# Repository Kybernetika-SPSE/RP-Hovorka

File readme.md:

# KYB Fotaoparát - Systém pro obsluhu kamery

## Zadání projektu
Cílem práce je návrh a realizace systému pro obsluhu
digitální kamery pomocí mikrokontroléru.

## Řešitelský tým
Vít Hovorka

## Vedoucí
Jiří Švihla

## Oponent
Pavel Jedlička

## Shrnutí projektu
Projekt „Fotaoparát" má za cíl navrhnout a realizovat řídicí systém pro digitální fotoaparát založený na mikrokontroléru ESP32‑P4. Práce kombinuje návrh hardware (schemata, PCB, periferie), mechanický návrh těla a vývoj firmware pro řízení kamery, paměti a uživatelského rozhraní.
## Fáze a plnění
## Termíny
| milník                                | termín              |
| :------------------------------------ | :------------------ |
| Nastudování dokumentací, návrh zapojení a design obalu| **30.12.2025** |
| Sestavení                         | **30.1.2026**  |
| Naprogramování operačního softwaru   | **27.2. 2026** |
| Testování a tvora dokumentace        | **30.03.2026** |
| Odevzdání ročníkové práce            | **30.04.2026** |

[^1]: Změněno na základě požadavků

### Ganttův diagram postupu
```mermaid
gantt
    title Milníky projektu
    dateFormat  YYYY-MM-DD
    axisFormat  %d.%m.%Y
    section Studium a návrh
    Studovat dokumentace a návrh   :done, study, 2025-09-01, 2025-12-30
    section Sestavení prototypu
    Montáž prototypu               :build, 2026-01-01, 2026-01-30
    section Vývoj softwaru
    Implementace firmware          :dev, 2026-02-01, 2026-02-27
    section Testování a dokumentace
    Testování a tvorba dokumentace :test, 2026-03-01, 2026-03-30
    section Odevzdání a prezentace
    Finalizace a odevzdání         :deliver, 2026-04-01, 2026-04-30
```

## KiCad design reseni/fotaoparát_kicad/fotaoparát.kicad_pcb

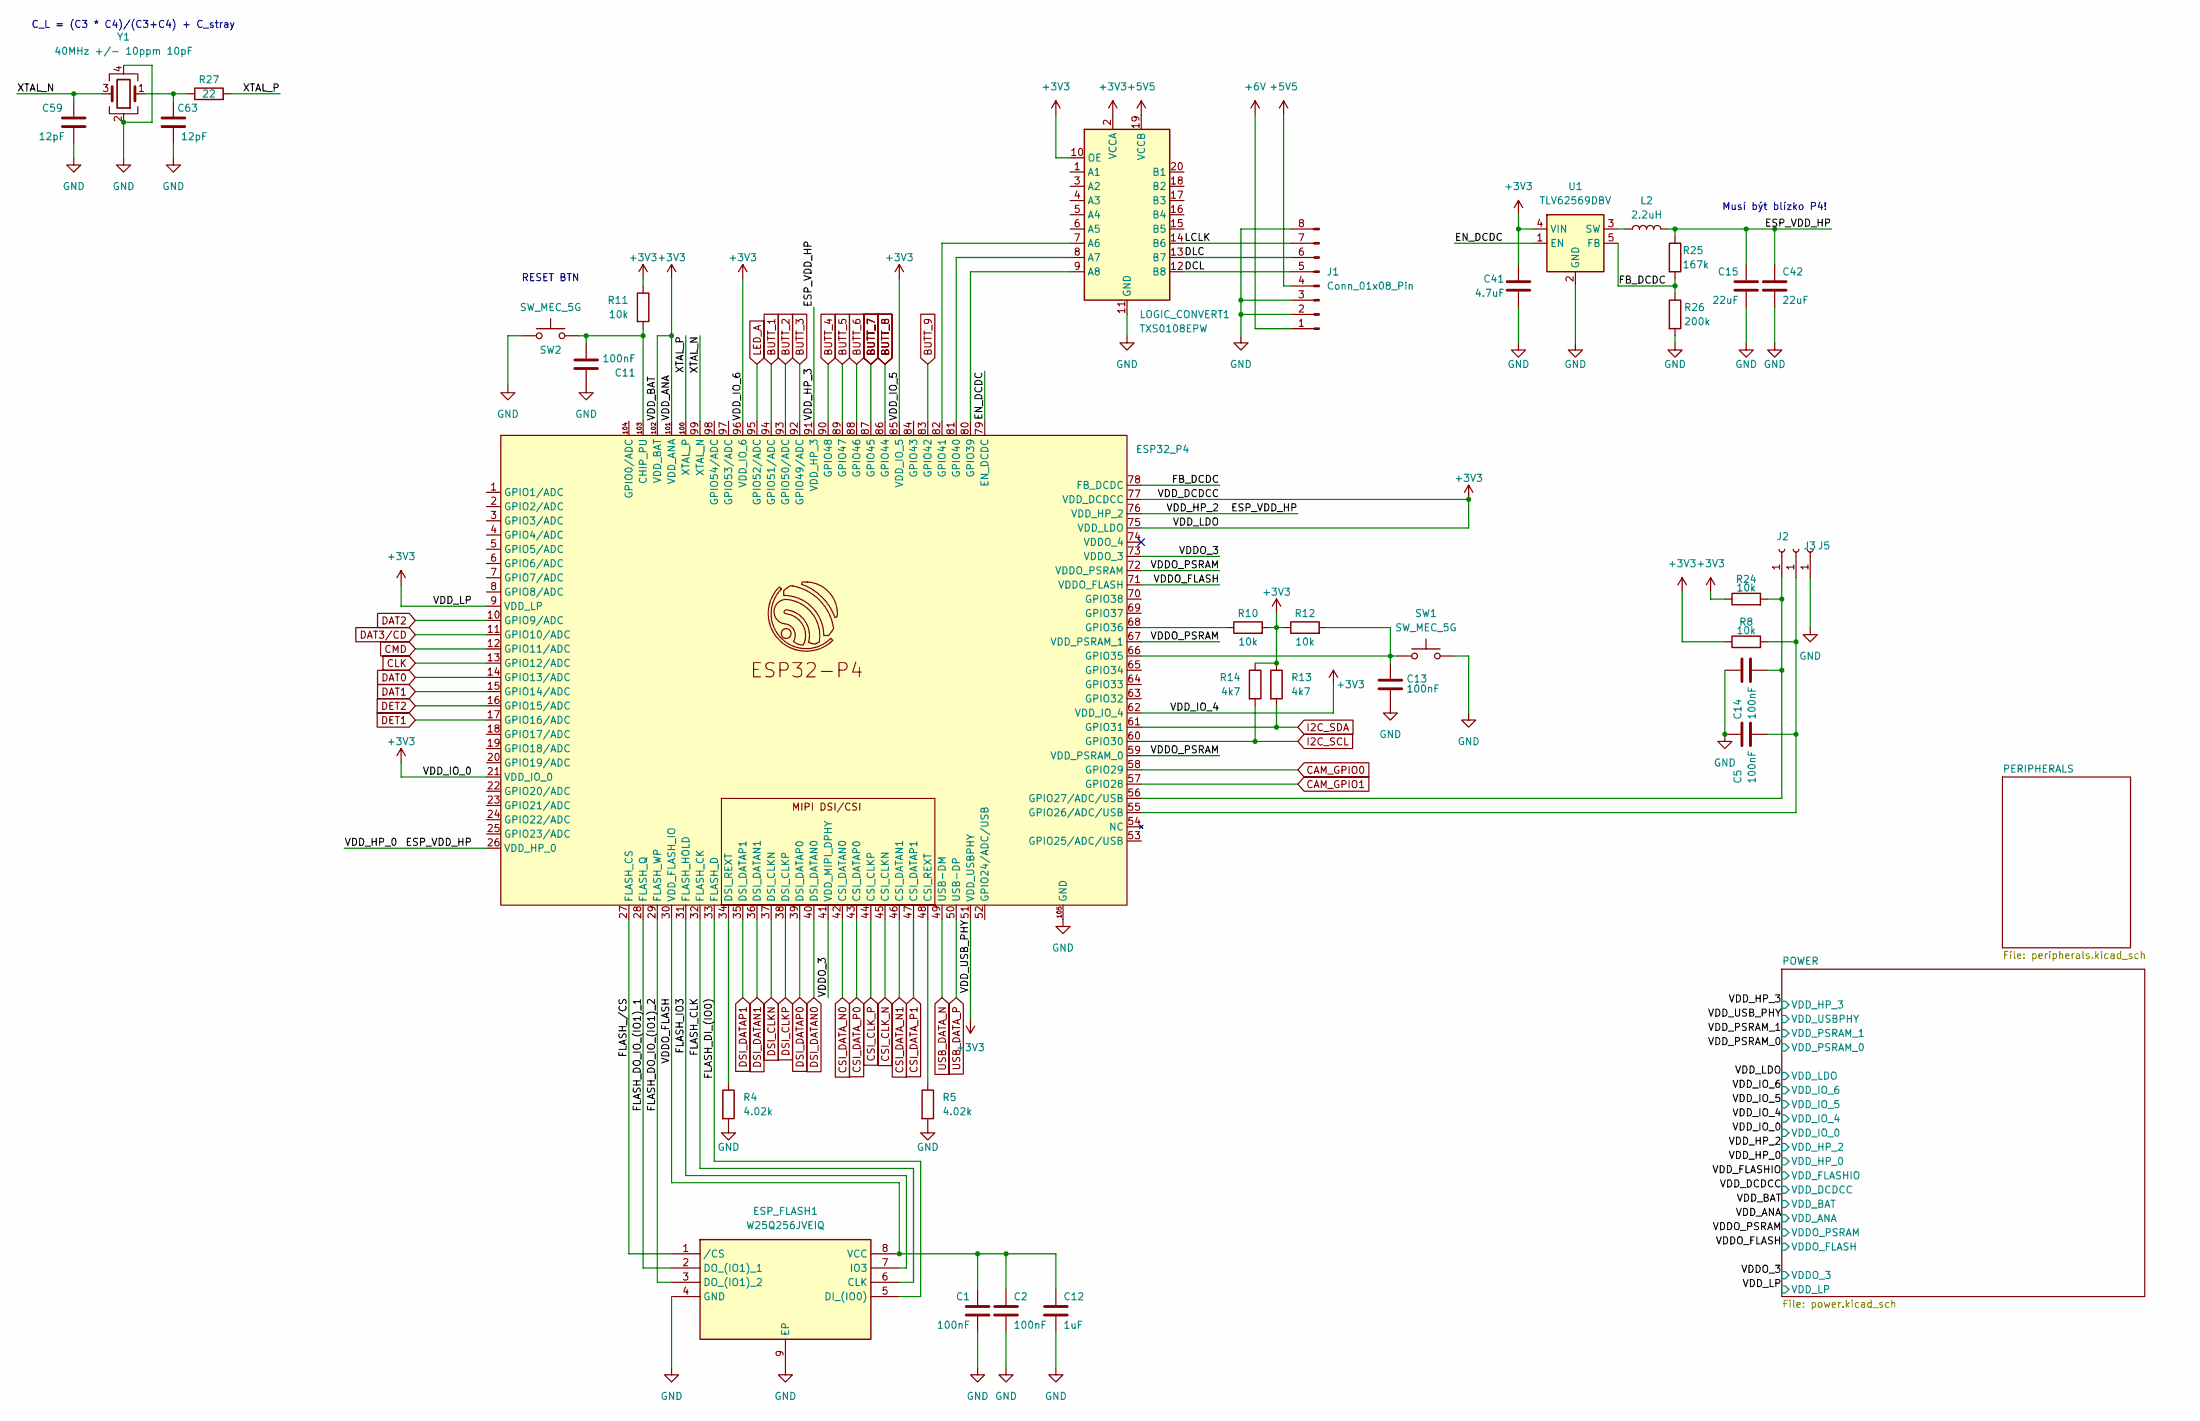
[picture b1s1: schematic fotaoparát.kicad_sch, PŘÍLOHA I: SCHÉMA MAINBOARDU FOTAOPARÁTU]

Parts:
C1, C2, C5, C11, C13, C14: 100nF; C_0201_0603Metric
C12: 1uF; C_0201_0603Metric
C15, C42: 22uF; C_0603_1608Metric
C41: 4.7uF; L_0603_1608Metric
C59, C63: 12pF; C_0402_1005Metric; LCSC Part C1547
ESP32_P4: ESP32_P4; ESP32-P4
ESP_FLASH1: W25Q256JVEIQ; SON127P800X600X80-9N-D; Mouser Part Number 454-W25Q256JVEIQ
J1: Conn_01x08_Pin; Amphenol_F32Q-1A7x1-11008_1x08-1MP_P0.5mm_Horizontal
J2, J3, J5: Conn_01x01_Socket; SolderWirePad_1x01_SMD_1.5x3mm
L2: 2.2uH; L_0603_1608Metric
LOGIC_CONVERT1: TXS0108EPW; TSSOP-20_4.4x6.5mm_P0.65mm
R4, R5: 4.02k; R_0603_1608Metric
R8, R10, R11, R12, R24: 10k; R_0603_1608Metric
R13, R14: 4k7; R_0603_1608Metric
R25: 167k; R_0603_1608Metric
R26: 200k; R_0603_1608Metric
R27: 22; R_0402_1005Metric; LCSC Part C25092
SW1, SW2: SW_MEC_5G; SW_Push_1P1T_NO_CK_KMR2
U1: TLV62569DBV; SOT-23-5
Y1: 40MHz +/- 10ppm 10pF; Crystal_SMD_2016-4Pin_2.0x1.6mm; LCSC Part C255898

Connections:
+5V5: J1.4, LOGIC_CONVERT1.19 (VCCB); also elsewhere on the board
+6V: J1.1; also elsewhere on the board
/DCL: J1.5, LOGIC_CONVERT1.12 (B8)
/DLC: J1.6, LOGIC_CONVERT1.13 (B7)
/EN_DCDC: ESP32_P4.79 (EN_DCDC), U1.1 (EN)
/FB_DCDC: ESP32_P4.78 (FB_DCDC), R25.2, R26.1, U1.5 (FB)
/FLASH_CLK: ESP32_P4.32 (FLASH_CK), ESP_FLASH1.6 (CLK)
/FLASH_DI_(IO0): ESP32_P4.33 (FLASH_D), ESP_FLASH1.5 (DI_(IO0))
/FLASH_DO_IO_(IO1)_1: ESP32_P4.28 (FLASH_Q), ESP_FLASH1.2 (DO_(IO1)_1)
/FLASH_DO_IO_(IO1)_2: ESP32_P4.29 (FLASH_WP), ESP_FLASH1.3 (DO_(IO1)_2)
/FLASH_IO3: ESP32_P4.31 (FLASH_HOLD), ESP_FLASH1.7 (IO3)
/FLASH_/CS: ESP32_P4.27 (FLASH_CS), ESP_FLASH1.1 (/CS)
/LCLK: J1.7, LOGIC_CONVERT1.14 (B6)
/VDDO_FLASH: C1.2, C2.2, C12.2, ESP32_P4.30 (VDD_FLASH_IO), ESP32_P4.71 (VDDO_FLASH), ESP_FLASH1.8 (VCC); also elsewhere on the board
/VDDO_PSRAM: ESP32_P4.59 (VDD_PSRAM_0), ESP32_P4.67 (VDD_PSRAM_1), ESP32_P4.72 (VDDO_PSRAM); also elsewhere on the board
/XTAL_N: C59.1, ESP32_P4.99 (XTAL_N), Y1.3
/XTAL_P: ESP32_P4.100 (XTAL_P), R27.2
BUTT_1: ESP32_P4.94 (GPIO51/ADC); also elsewhere on the board
BUTT_2: ESP32_P4.93 (GPIO50/ADC); also elsewhere on the board
BUTT_3: ESP32_P4.92 (GPIO49/ADC); also elsewhere on the board
BUTT_4: ESP32_P4.90 (GPIO48); also elsewhere on the board
BUTT_5: ESP32_P4.89 (GPIO47); also elsewhere on the board
BUTT_6: ESP32_P4.88 (GPIO46); also elsewhere on the board
BUTT_7: ESP32_P4.87 (GPIO45); also elsewhere on the board
BUTT_8: ESP32_P4.86 (GPIO44); also elsewhere on the board
BUTT_9: ESP32_P4.83 (GPIO42); also elsewhere on the board
CAM_GPIO0: ESP32_P4.58 (GPIO29); also elsewhere on the board
CAM_GPIO1: ESP32_P4.57 (GPIO28); also elsewhere on the board
CLK: ESP32_P4.13 (GPIO12/ADC); also elsewhere on the board
CMD: ESP32_P4.12 (GPIO11/ADC); also elsewhere on the board
CSI_CLK_N: ESP32_P4.45 (CSI_CLKN); also elsewhere on the board
CSI_CLK_P: ESP32_P4.44 (CSI_CLKP); also elsewhere on the board
CSI_DATA_N0: ESP32_P4.42 (CSI_DATAN0); also elsewhere on the board
CSI_DATA_N1: ESP32_P4.46 (CSI_DATAN1); also elsewhere on the board
CSI_DATA_P0: ESP32_P4.43 (CSI_DATAP0); also elsewhere on the board
CSI_DATA_P1: ESP32_P4.47 (CSI_DATAP1); also elsewhere on the board
DAT0: ESP32_P4.14 (GPIO13/ADC); also elsewhere on the board
DAT1: ESP32_P4.15 (GPIO14/ADC); also elsewhere on the board
DAT2: ESP32_P4.10 (GPIO9/ADC); also elsewhere on the board
DAT3/CD: ESP32_P4.11 (GPIO10/ADC); also elsewhere on the board
DET1: ESP32_P4.17 (GPIO16/ADC); also elsewhere on the board
DET2: ESP32_P4.16 (GPIO15/ADC); also elsewhere on the board
DSI_CLKN: ESP32_P4.37 (DSI_CLKN); also elsewhere on the board
DSI_CLKP: ESP32_P4.38 (DSI_CLKP); also elsewhere on the board
DSI_DATAN0: ESP32_P4.40 (DSI_DATAN0); also elsewhere on the board
DSI_DATAN1: ESP32_P4.36 (DSI_DATAN1); also elsewhere on the board
DSI_DATAP0: ESP32_P4.39 (DSI_DATAP0); also elsewhere on the board
DSI_DATAP1: ESP32_P4.35 (DSI_DATAP1); also elsewhere on the board
I2C_SCL: ESP32_P4.60 (GPIO30), R14.2; also elsewhere on the board
I2C_SDA: ESP32_P4.61 (GPIO31), R13.2; also elsewhere on the board
LED_A: ESP32_P4.95 (GPIO52/ADC); also elsewhere on the board
unnamed: C63.1, R27.1, Y1.1
unnamed: C11.2, ESP32_P4.103 (CHIP_PU), R11.2, SW2.3 (B), SW2.4 (B)
unnamed: ESP32_P4.48 (CSI_REXT), R5.1
unnamed: ESP32_P4.34 (DSI_REXT), R4.1
unnamed: C5.2, ESP32_P4.55 (GPIO26/ADC/USB), J3.1 (Pin_1_1), R8.2
unnamed: C14.2, ESP32_P4.56 (GPIO27/ADC/USB), J2.1 (Pin_1_1), R24.2
unnamed: C13.1, ESP32_P4.66 (GPIO35), R12.2, SW1.1 (A), SW1.2 (A)
unnamed: ESP32_P4.68 (GPIO36), R10.1
unnamed: ESP32_P4.80 (GPIO39), LOGIC_CONVERT1.9 (A8)
unnamed: ESP32_P4.81 (GPIO40), LOGIC_CONVERT1.8 (A7)
unnamed: ESP32_P4.82 (GPIO41), LOGIC_CONVERT1.7 (A6)
unnamed: L2.1, U1.3 (SW)
USB_DATA_N: ESP32_P4.49 (USB-DM); also elsewhere on the board
USB_DATA_P: ESP32_P4.50 (USB-DP); also elsewhere on the board

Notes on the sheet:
C_L = (C3 * C4)/(C3+C4) + C_stray
RESET BTN
Musí být blízko P4!

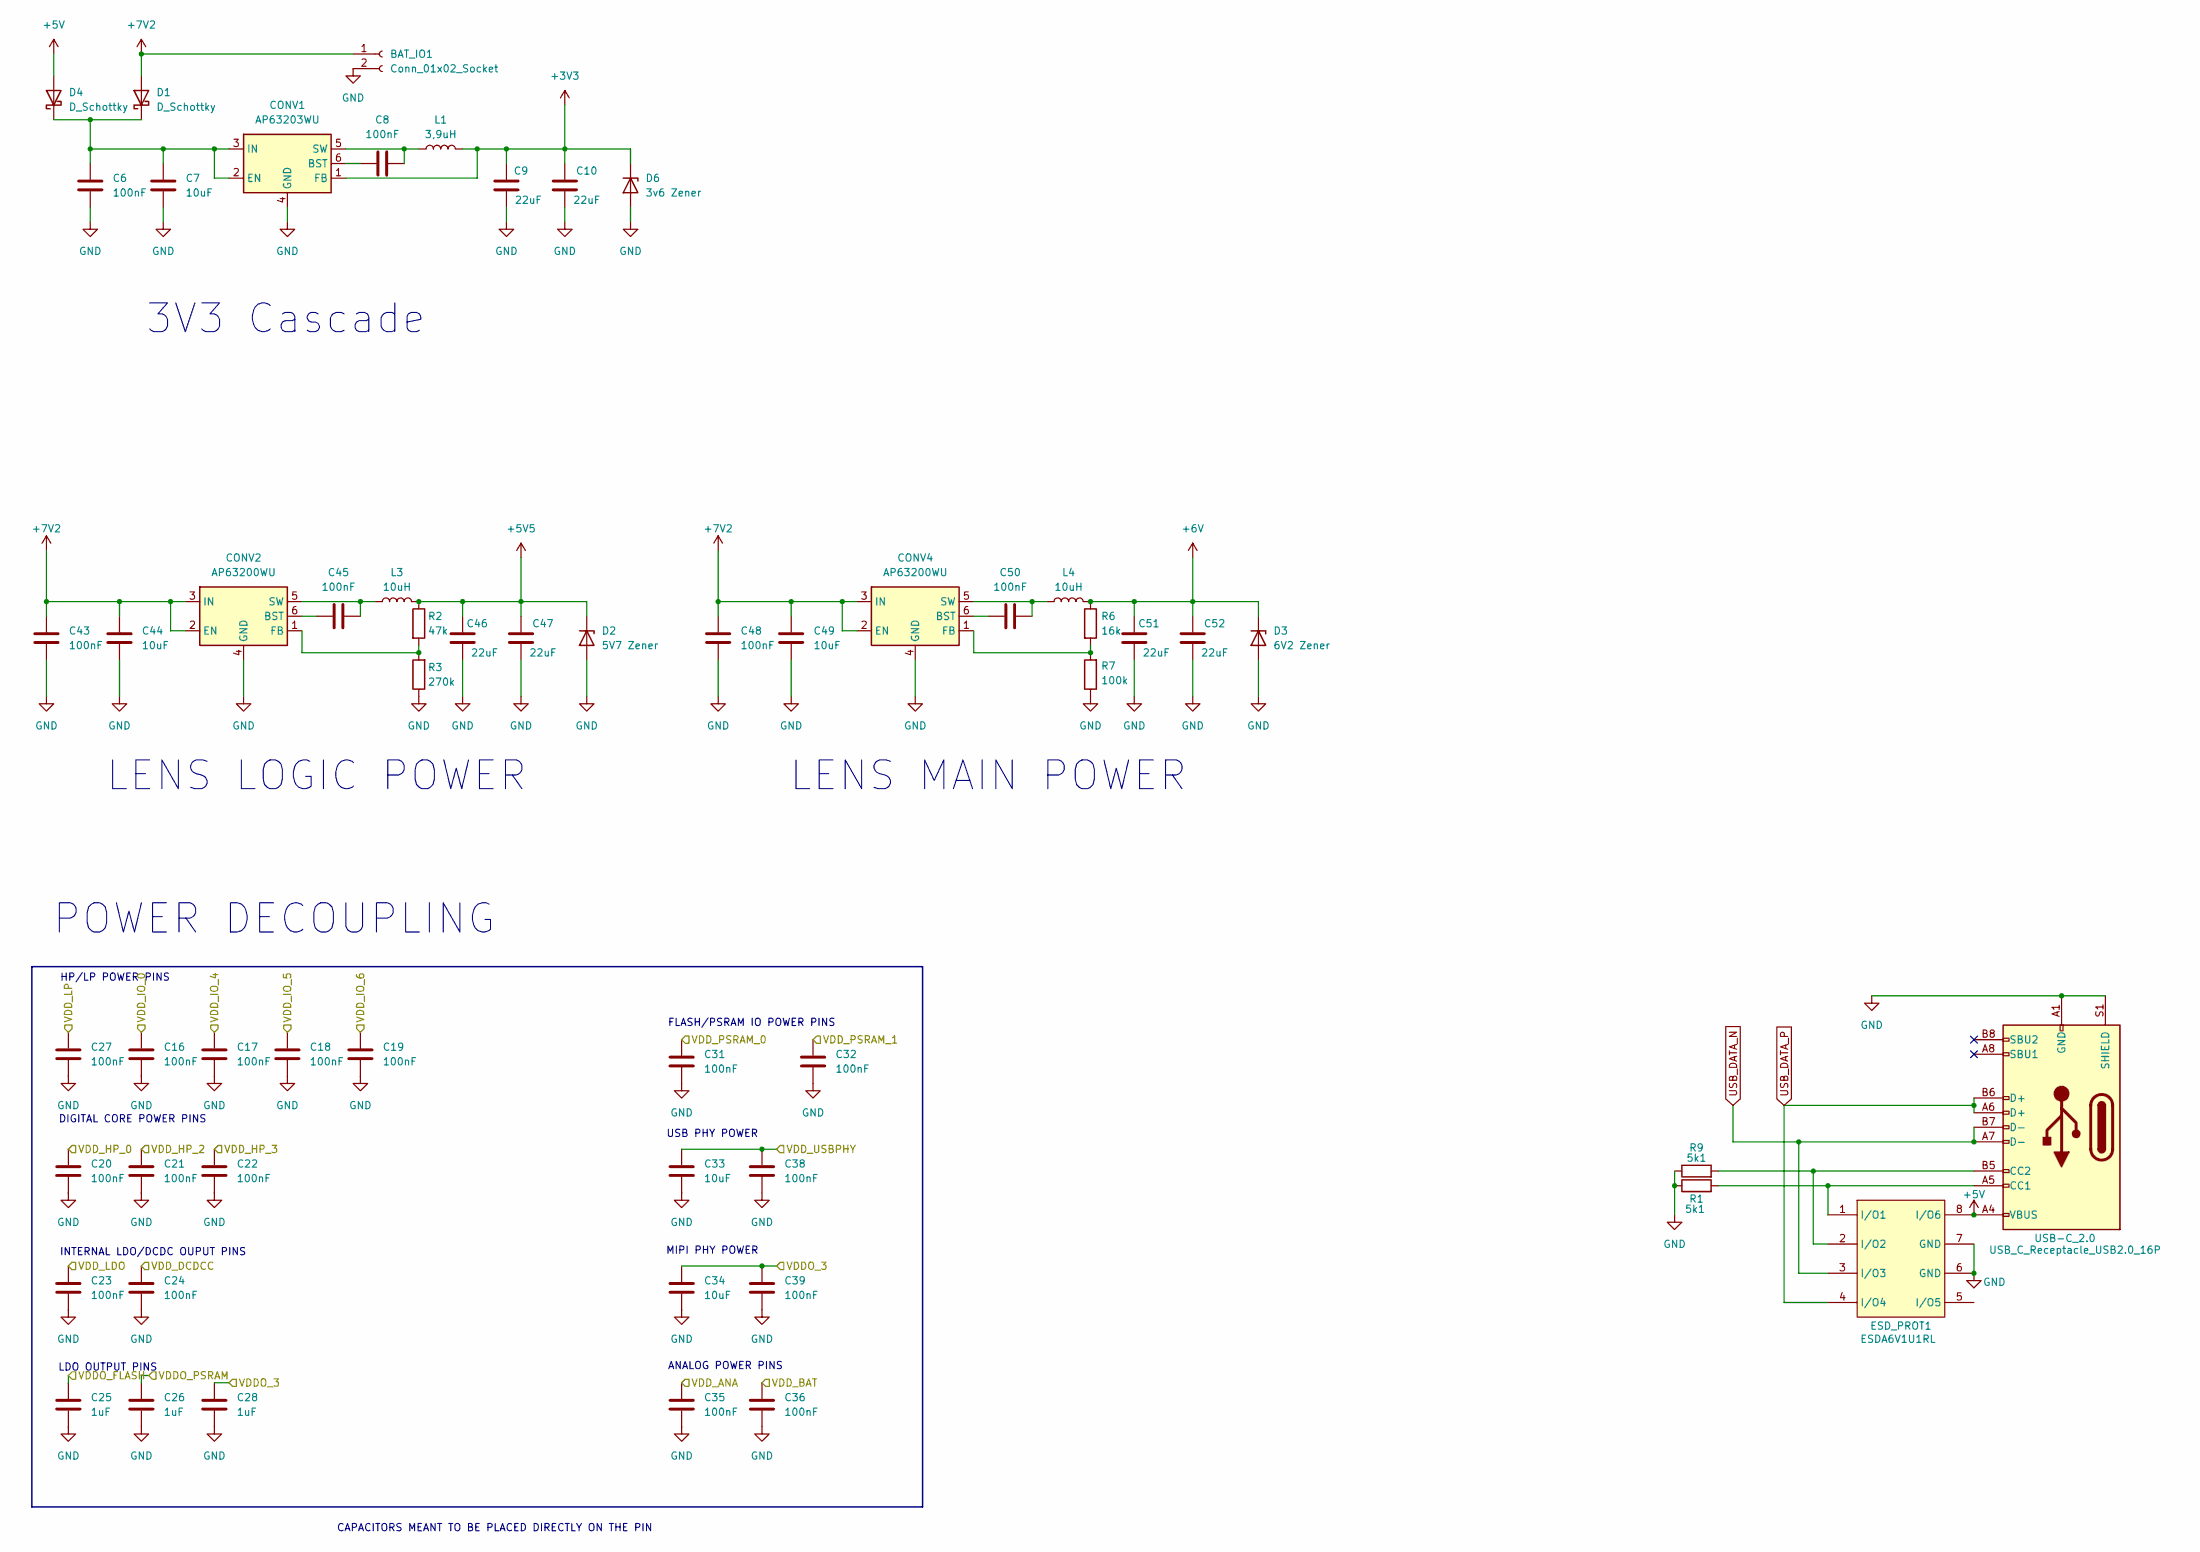
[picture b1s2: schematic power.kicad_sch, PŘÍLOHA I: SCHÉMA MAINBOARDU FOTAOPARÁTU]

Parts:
BAT_IO1: Conn_01x02_Socket; SolderWire-1.5sqmm_1x02_P6mm_D1.7mm_OD3mm
C6, C8, C43, C45, C48, C50: 100nF; C_0603_1608Metric; LCSC C14663
C7, C44, C49: 10uF; C_0603_1608Metric; LCSC C19702
C9, C10, C46, C47, C51, C52: 22uF; C_0603_1608Metric; LCSC C59461
C16, C17, C18, C19, C20, C21, C22, C23, C24, C27, C31, C32, C35, C36, C38, C39: 100nF; C_0201_0603Metric
C25, C26, C28: 1uF; C_0201_0603Metric
C33, C34: 10uF; C_0201_0603Metric
CONV1: AP63203WU; TSOT-23-6; LCSC C780769
CONV2, CONV4: AP63200WU; TSOT-23-6
D1, D4: D_Schottky; D_0805_2012Metric
D2: 5V7 Zener; D_SOD-123; LCSC Part C66886
D3: 6V2 Zener; D_SOD-123; LCSC Part C66886
D6: 3v6 Zener; D_SOD-123; LCSC Part C66886
ESD_PROT1: ESDA6V1U1RL; SO-8_L4.9-W3.9-P1.27-LS5.9-BL; LCSC Part C118278
L1: 3,9uH; L_0603_1608Metric; LCSC C915148
L3, L4: 10uH; L_0603_1608Metric; LCSC C915148
R1, R9: 5k1; R_0603_1608Metric
R2: 47k; R_0603_1608Metric
R3: 270k; R_0603_1608Metric
R6: 16k; R_0603_1608Metric
R7: 100k; R_0603_1608Metric
USB-C_2.0: USB_C_Receptacle_USB2.0_16P; USB_C_Receptacle_Palconn_UTC16-G

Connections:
+5V: D4.2 (A), ESD_PROT1.8 (I/O6), USB-C_2.0.A4 (VBUS), USB-C_2.0.A9 (VBUS), USB-C_2.0.B4 (VBUS), USB-C_2.0.B9 (VBUS)
+5V5: C46.2, C47.2, D2.1 (K), L3.2, R2.1; also elsewhere on the board
+6V: C51.2, C52.2, D3.1 (K), L4.2, R6.1; also elsewhere on the board
+7V2: BAT_IO1.1, C43.2, C44.2, C48.2, C49.2, CONV2.2 (EN), CONV2.3 (IN), CONV4.2 (EN), CONV4.3 (IN), D1.2 (A)
/VDDO_FLASH: C31.1; also elsewhere on the board
/VDDO_PSRAM: C32.1; also elsewhere on the board
unnamed: C8.1, CONV1.6 (BST)
unnamed: C6.2, C7.2, CONV1.2 (EN), CONV1.3 (IN), D1.1 (K), D4.1 (K)
unnamed: C8.2, CONV1.5 (SW), L1.1
unnamed: C45.1, CONV2.6 (BST)
unnamed: CONV2.1 (FB), R2.2, R3.2
unnamed: C45.2, CONV2.5 (SW), L3.1
unnamed: C50.1, CONV4.6 (BST)
unnamed: CONV4.1 (FB), R6.2, R7.2
unnamed: C50.2, CONV4.5 (SW), L4.1
unnamed: ESD_PROT1.1 (I/O1), R1.2, USB-C_2.0.A5 (CC1)
unnamed: ESD_PROT1.2 (I/O2), R9.2, USB-C_2.0.B5 (CC2)
USB_DATA_N: ESD_PROT1.3 (I/O3), USB-C_2.0.A7 (D-), USB-C_2.0.B7 (D-); also elsewhere on the board
USB_DATA_P: ESD_PROT1.4 (I/O4), USB-C_2.0.A6 (D+), USB-C_2.0.B6 (D+); also elsewhere on the board

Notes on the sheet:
CAPACITORS MEANT TO BE PLACED DIRECTLY ON THE PIN
LENS LOGIC POWER
FLASH/PSRAM IO POWER PINS
USB PHY POWER
DIGITAL CORE POWER PINS
MIPI PHY POWER
POWER DECOUPLING
HP/LP POWER PINS
LDO OUTPUT PINS
ANALOG POWER PINS
INTERNAL LDO/DCDC OUPUT PINS
3V3 Cascade
LENS MAIN POWER

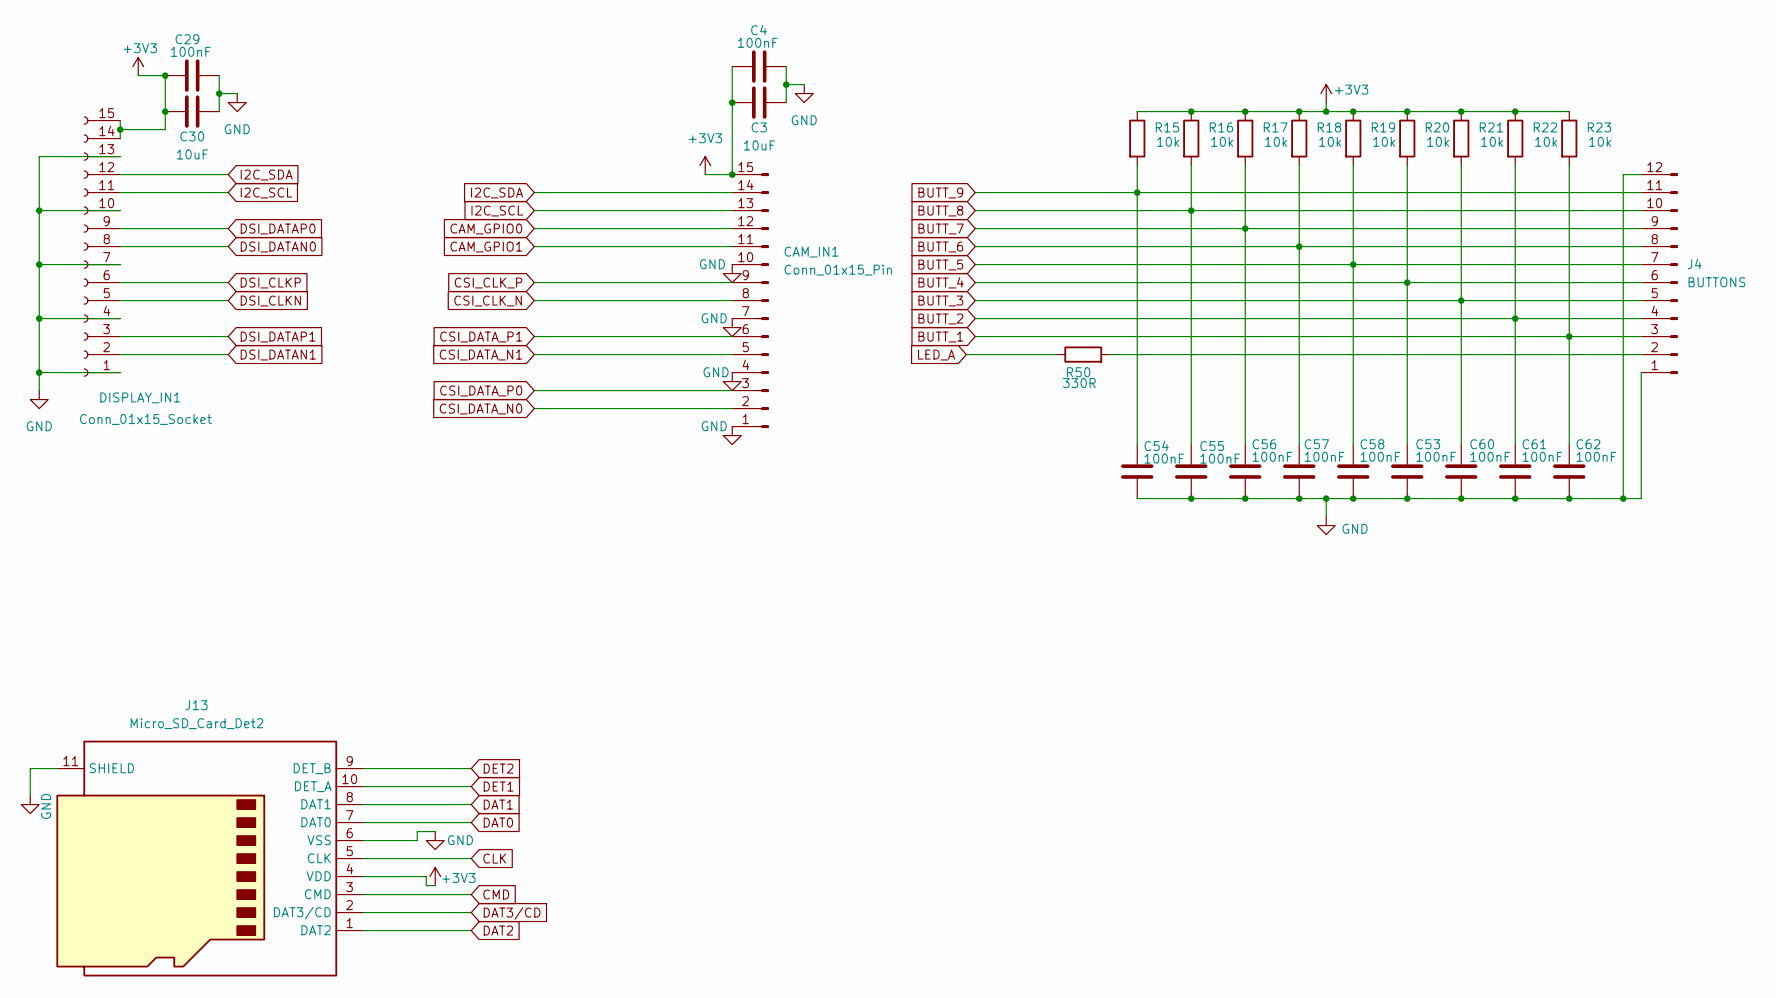
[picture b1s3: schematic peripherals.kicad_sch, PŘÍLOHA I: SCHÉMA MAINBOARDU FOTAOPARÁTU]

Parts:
C3, C30: 10uF; C_0603_1608Metric
C4, C29, C53, C54, C55, C56, C57, C58, C60, C61, C62: 100nF; C_0201_0603Metric
CAM_IN1: Conn_01x15_Pin; Hirose_FH12-15S-0.5SH_1x15-1MP_P0.50mm_Horizontal
DISPLAY_IN1: Conn_01x15_Socket; Hirose_FH12-15S-0.5SH_1x15-1MP_P0.50mm_Horizontal
J4: BUTTONS; Hirose_FH12-12S-0.5SH_1x12-1MP_P0.50mm_Horizontal
J13: Micro_SD_Card_Det2; microSD_HC_Hirose_DM3BT-DSF-PEJS
R15, R16, R17, R18, R19, R20, R21, R22, R23: 10k; R_0603_1608Metric
R50: 330R; R_0603_1608Metric

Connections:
BUTT_1: C62.1, J4.3, R23.2; also elsewhere on the board
BUTT_2: C61.1, J4.4, R22.2; also elsewhere on the board
BUTT_3: C60.1, J4.5, R21.2; also elsewhere on the board
BUTT_4: C53.1, J4.6, R20.2; also elsewhere on the board
BUTT_5: C58.1, J4.7, R19.2; also elsewhere on the board
BUTT_6: C57.1, J4.8, R18.2; also elsewhere on the board
BUTT_7: C56.1, J4.9, R17.2; also elsewhere on the board
BUTT_8: C55.1, J4.10, R16.2; also elsewhere on the board
BUTT_9: C54.1, J4.11, R15.2; also elsewhere on the board
CAM_GPIO0: CAM_IN1.12; also elsewhere on the board
CAM_GPIO1: CAM_IN1.11; also elsewhere on the board
CLK: J13.5 (CLK); also elsewhere on the board
CMD: J13.3 (CMD); also elsewhere on the board
CSI_CLK_N: CAM_IN1.8; also elsewhere on the board
CSI_CLK_P: CAM_IN1.9; also elsewhere on the board
CSI_DATA_N0: CAM_IN1.2; also elsewhere on the board
CSI_DATA_N1: CAM_IN1.5; also elsewhere on the board
CSI_DATA_P0: CAM_IN1.3; also elsewhere on the board
CSI_DATA_P1: CAM_IN1.6; also elsewhere on the board
DAT0: J13.7 (DAT0); also elsewhere on the board
DAT1: J13.8 (DAT1); also elsewhere on the board
DAT2: J13.1 (DAT2); also elsewhere on the board
DAT3/CD: J13.2 (DAT3/CD); also elsewhere on the board
DET1: J13.10 (DET_A); also elsewhere on the board
DET2: J13.9 (DET_B); also elsewhere on the board
DSI_CLKN: DISPLAY_IN1.5; also elsewhere on the board
DSI_CLKP: DISPLAY_IN1.6; also elsewhere on the board
DSI_DATAN0: DISPLAY_IN1.8; also elsewhere on the board
DSI_DATAN1: DISPLAY_IN1.2; also elsewhere on the board
DSI_DATAP0: DISPLAY_IN1.9; also elsewhere on the board
DSI_DATAP1: DISPLAY_IN1.3; also elsewhere on the board
I2C_SCL: CAM_IN1.13, DISPLAY_IN1.11; also elsewhere on the board
I2C_SDA: CAM_IN1.14, DISPLAY_IN1.12; also elsewhere on the board
LED_A: R50.1; also elsewhere on the board
unnamed: J4.2, R50.2

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
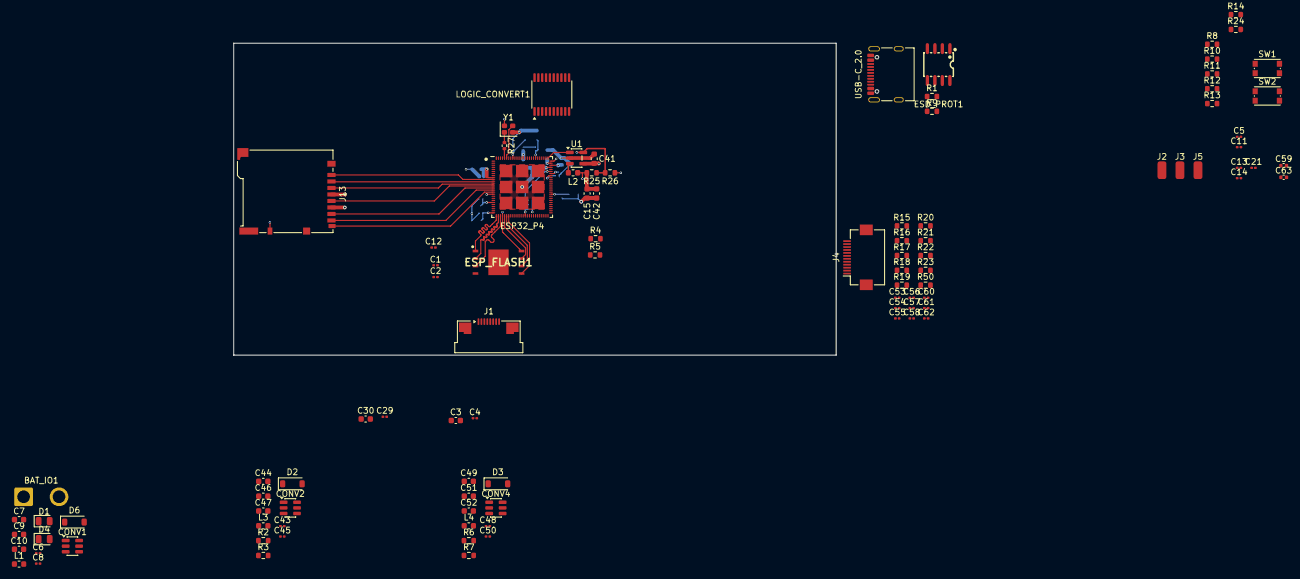
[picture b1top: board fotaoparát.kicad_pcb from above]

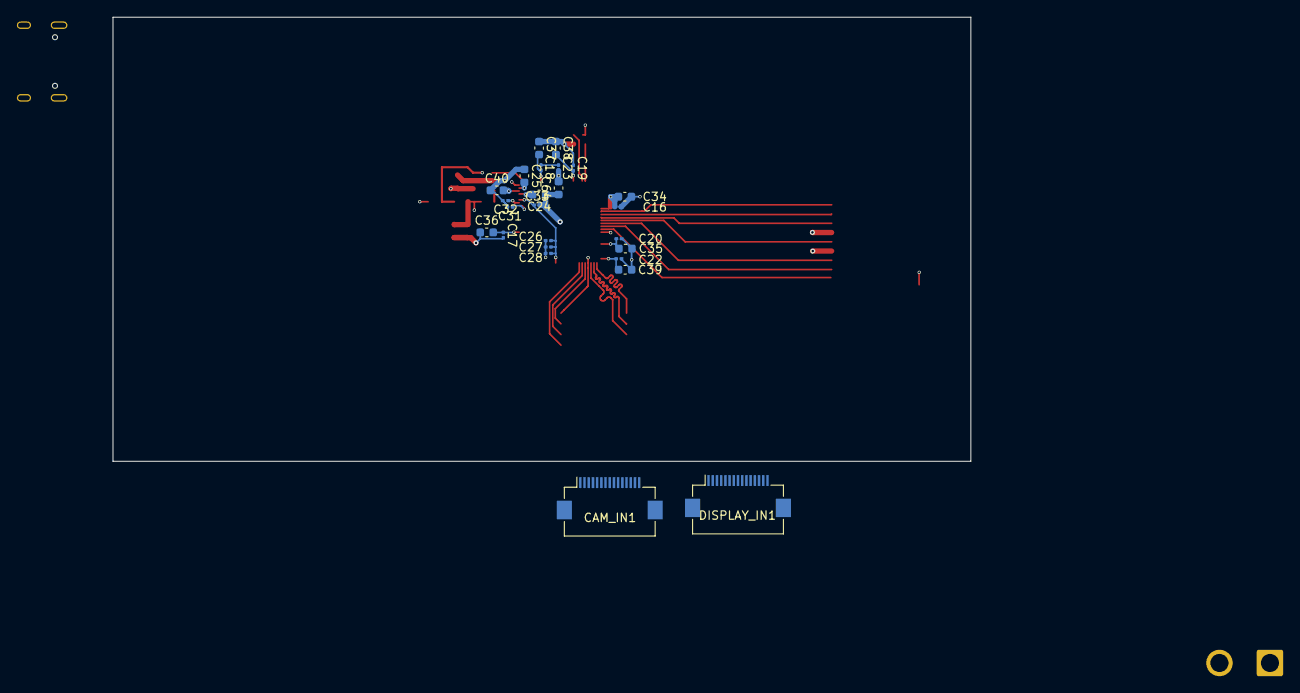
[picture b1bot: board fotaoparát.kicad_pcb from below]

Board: 4 copper layers, 102.0 x 52.8 mm, 122 parts (25 on the bottom side), 83 nets.

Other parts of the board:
C37, C40, C64: 10uF; C_0603_1608Metric

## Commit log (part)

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2025-11-15 pridani readme
2025-11-15 pridani souboru s zadanim RP TL 25 26
2025-11-16 Rename Zadani_RP_TL_24_25.docx to Zadani-Hovorka.docx
2025-11-29 Datasheeshty
2025-11-30 Oprava adresare
2025-12-08 prejmenovani pro lepsi orientaci (jsem delulu)
2025-12-08 idk co to je ale chic aby to zmizelo
2025-12-11 blablabla
2025-12-11 Pridani PCB, s a lcd + datasheety
2025-12-13 nevim, neco tu vadi
2025-12-17 Mirne nakresove zmeny
2025-12-18 PCB routing 22pin na kameru
2025-12-19 Add MIPI_CSI2 and FLASH_BUS netclasses and assign via netclass_patterns
2025-12-21 Uprava pcb, finalni predelani (snad) kamery
2025-12-22 Zvyseni prehlednosti schametu
2025-12-28 Add link and note about display usage
2026-01-09 Udelal jsem znovu sd kartovy dock, tentokrat je spravne orientovany to same s konktorem na display
2026-01-09 Upraveni routingu pro zlepseni kvality signalu
    musim predelat cely konktor na display
2026-01-17 Tech zmen je tolik ze ani nevim co napsat Rerouting v podstate vseho, znovu predelani displaye, flash, sd kartoveho holderu
2026-01-23 Add lens_logic.py for interfacing with Canon EF lens using ESP32
2026-01-23 delani pullups
2026-01-23 ai pomoc (citace a program na optiku)
2026-01-24 delal jsem pullups
2026-01-25 Udelani USB-C konektoru, reset a flash tlacitek
2026-01-25 commit backup souboru, jenom me to rusi, lze ignorovat
2026-01-28 Delal jsem znova flash, predelal jsem usb-c konektor a display konektor
2026-01-28 nejake nesrovnalosti
2026-01-28 aaaaaaaaaaaaaaaaaaaaaaaaaaaaaaaaaaaa
2026-01-30 optimalizace routingu, oprava chyb, pridani baterky do soupisu mimo pcb
2026-01-30 Vymena displaye za mensi
2026-02-01 Predelani 80 % routingu pro optimalizaci mista na desce, a predelani napajeni do 7,2V akumulatoru.
2026-02-01 vice optimalizace
2026-02-02 bla bla bla decoupling
2026-02-05 Rerouting CSI/DSI rozhrani
2026-02-05 NEvim co to je za bordel ale modlim se
2026-02-05 mirne korekce
2026-02-10 Pridani krystalu
2026-02-11 Delani delani, dalsi pcb vytvari ztracim svou mysl
2026-02-15 Expand README with hardware requirements and checks
    Added detailed hardware TODOs and double-checks before production.
2026-02-19 Předělání powerrials, přidání malého pcb na spousť foťáku
2026-02-19 Neco se tam rozjelo, i2c korekce
2026-02-21 neco
2026-02-22 Pridani konektoru pro tlacitka na schema
2026-02-23 Update readme with Canon 550D pinout and LED info
    Added details about the Canon 550D button pinout and LED status indicators.
2026-02-23 XDD NEVIM ZABIJU SE
2026-02-23 Udelal jsem pullupy na tlacitka z fotaku
2026-02-28 Pridani asi poloviny lscs cisel
2026-03-01 PRidani (skoro) vsech lscs cisel, krystal je spatne ale pcb mam doma udelane jeste jinak, takze pridam a preroutuju pozdeji.
2026-03-04 FInalni doteky. Ted uz jenom opravy {snad}
2026-03-16 Udelal jsem: -Predelani labelu na global -Pridani vyvodu na desku pro spoust -Pokusil se predelat ten stepdown, Vout by mela byt 1V1, nestihl jsem prepsat vsechny hodnoty a pridat lscs cisla
2026-03-17 Dodelani stepdownu, prirazeni lscs cisel
2026-03-20 nejaky maly zmeny asi
2026-03-25 [1/6] Úklid a opravy toho nejnutnějšího na hlavní straně schématu
2026-04-04 Předělání struktury adresářů, přidání poznámek k protokolu a přidání základů pro backend a firmware.
2026-04-23 Uprava textu a zapojeni v dokumentaci
2026-04-27 Update KiCad project and documentation
2026-04-28 Prace na dokumentaci
2026-04-28 Zmeny na domacim pc
2026-04-28 nece neco
2026-04-28 pokracovani v dokumentaci
2026-04-29 uprava adresaru
2026-04-29 Priprava na finalni upravu PDF
2026-04-30 uprava adresaru, finani odevzdani
2026-06-30 je to bordel, snad bude ale fungovat
